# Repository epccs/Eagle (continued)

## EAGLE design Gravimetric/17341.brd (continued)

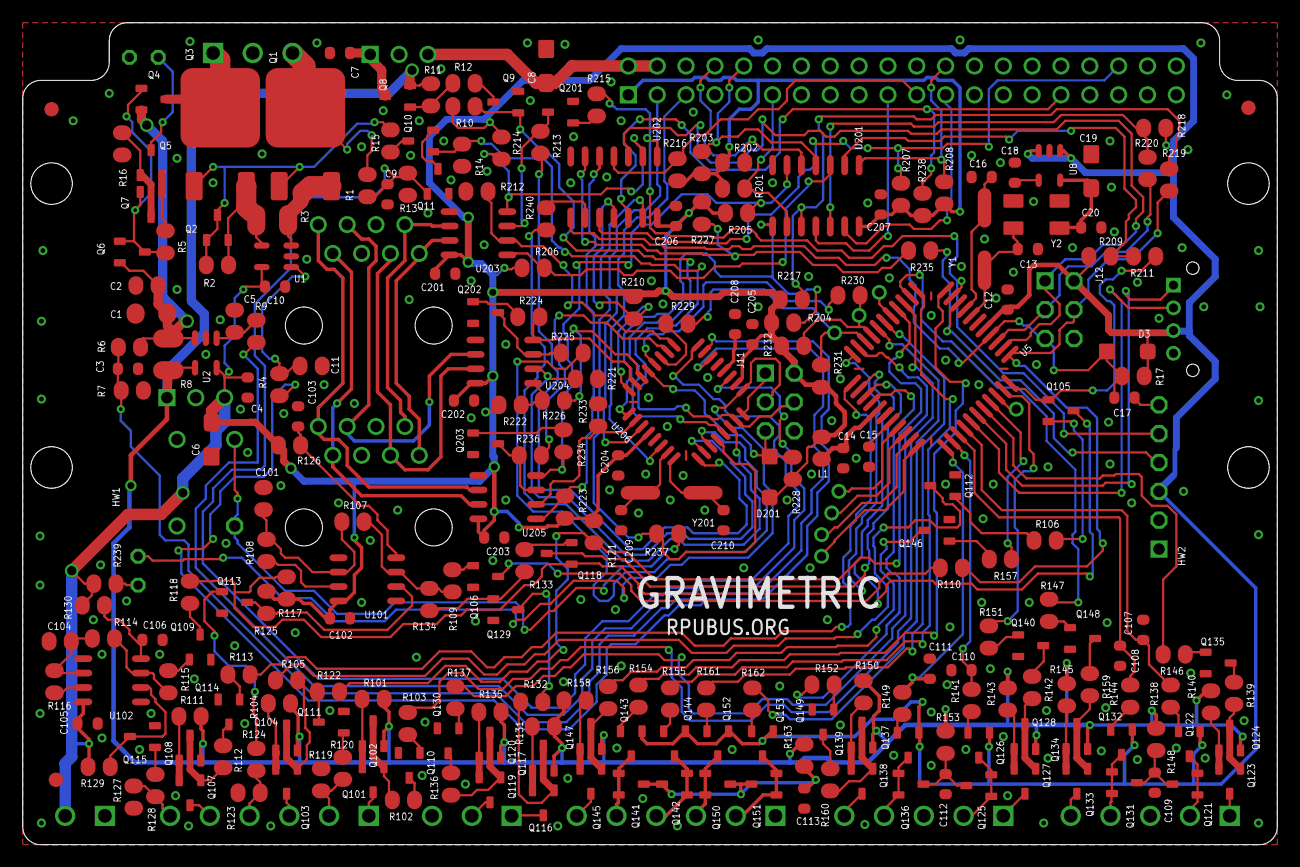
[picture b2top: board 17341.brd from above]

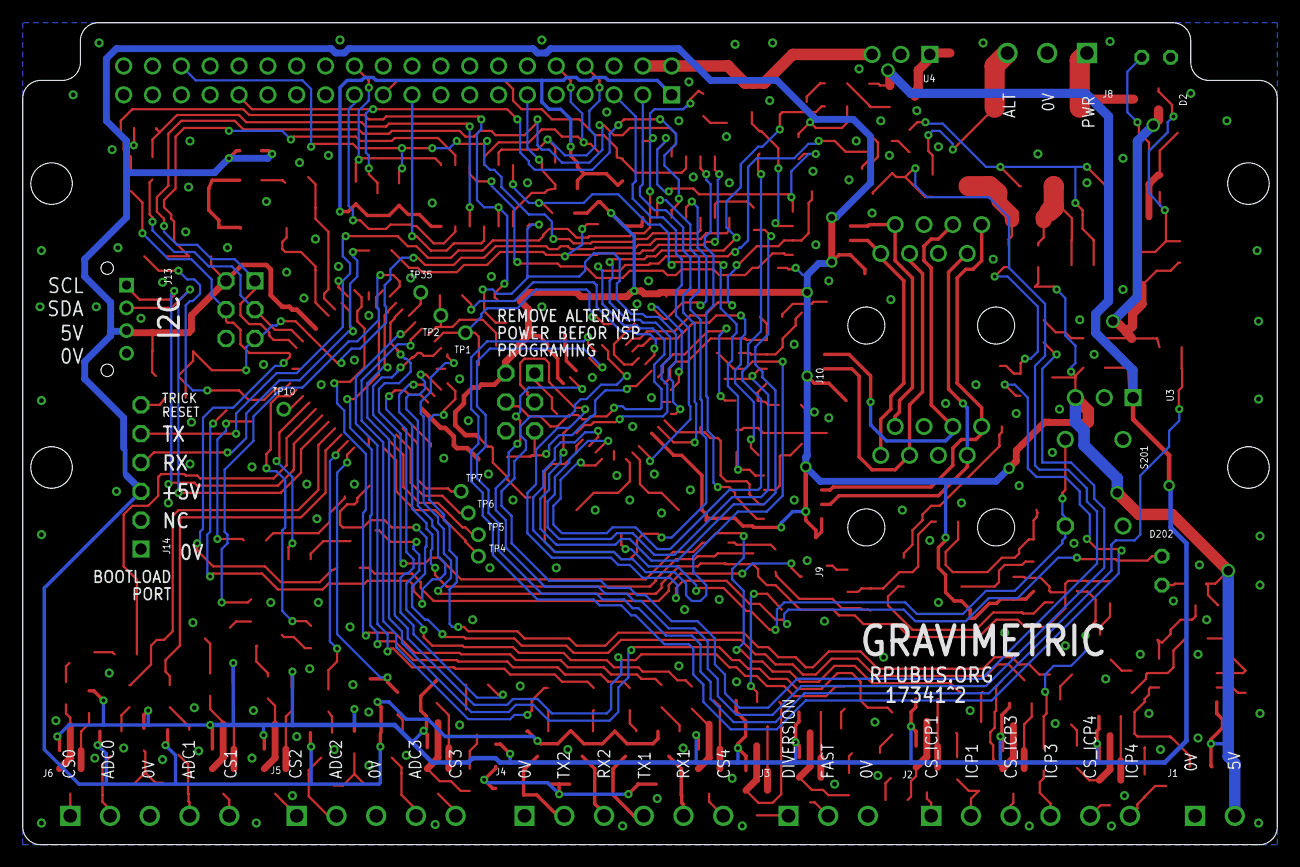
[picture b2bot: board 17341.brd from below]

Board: 2 copper layers, 110.5 x 72.4 mm, 281 parts (26 on the bottom side), 219 nets.

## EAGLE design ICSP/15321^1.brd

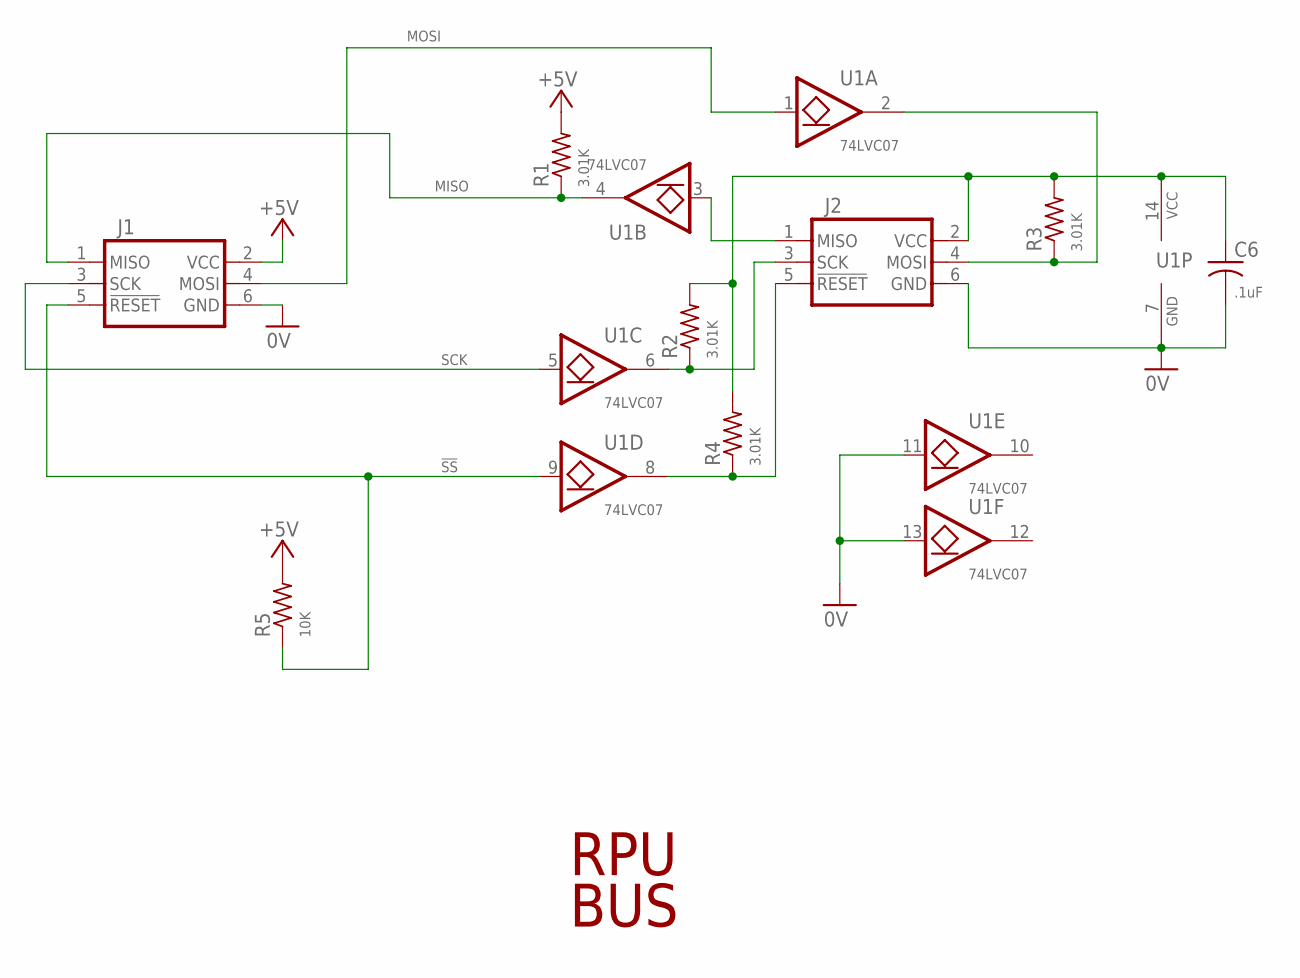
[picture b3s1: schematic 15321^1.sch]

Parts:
C6: .1uF; C0603(1608)
J1, J2: ISP-SPIEDG; ISP-EDG
R1, R2, R3, R4: 3.01K; C0805(2012)
R5: 10K; C0805(2012)
U1: 74LVC07; 14SOIC

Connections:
0V: C6.2, J1.6 (GND), J2.6 (GND), U1.7 (GND), U1.11 (I), U1.13 (I)
!SS: J1.5 (!RESET), R5.1, U1.9 (I)
+5V: J1.2 (VCC), R1.2, R5.2
MISO: J1.1 (MISO), R1.1, U1.4 (O)
MOSI: J1.4 (MOSI), U1.1 (I)
unnamed: J2.3 (SCK), R2.1, U1.6 (O)
unnamed: J2.1 (MISO), U1.3 (I)
unnamed: J2.4 (MOSI), R3.1, U1.2 (O)
unnamed: J2.5 (!RESET), R4.1, U1.8 (O)
SCK: J1.3 (SCK), U1.5 (I)
VCC: C6.1, J2.2 (VCC), R2.2, R3.2, R4.2, U1.14 (VCC)

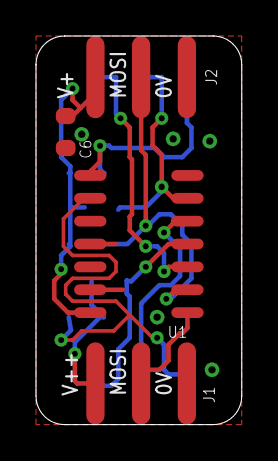
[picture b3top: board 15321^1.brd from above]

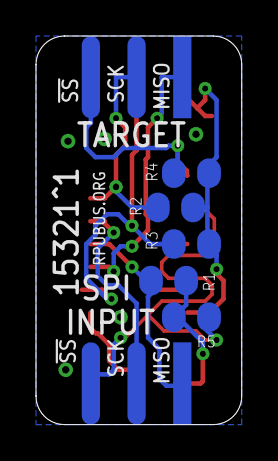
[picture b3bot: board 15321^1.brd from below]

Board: 2 copper layers, 11.4 x 21.6 mm, 9 parts (5 on the bottom side), 11 nets.

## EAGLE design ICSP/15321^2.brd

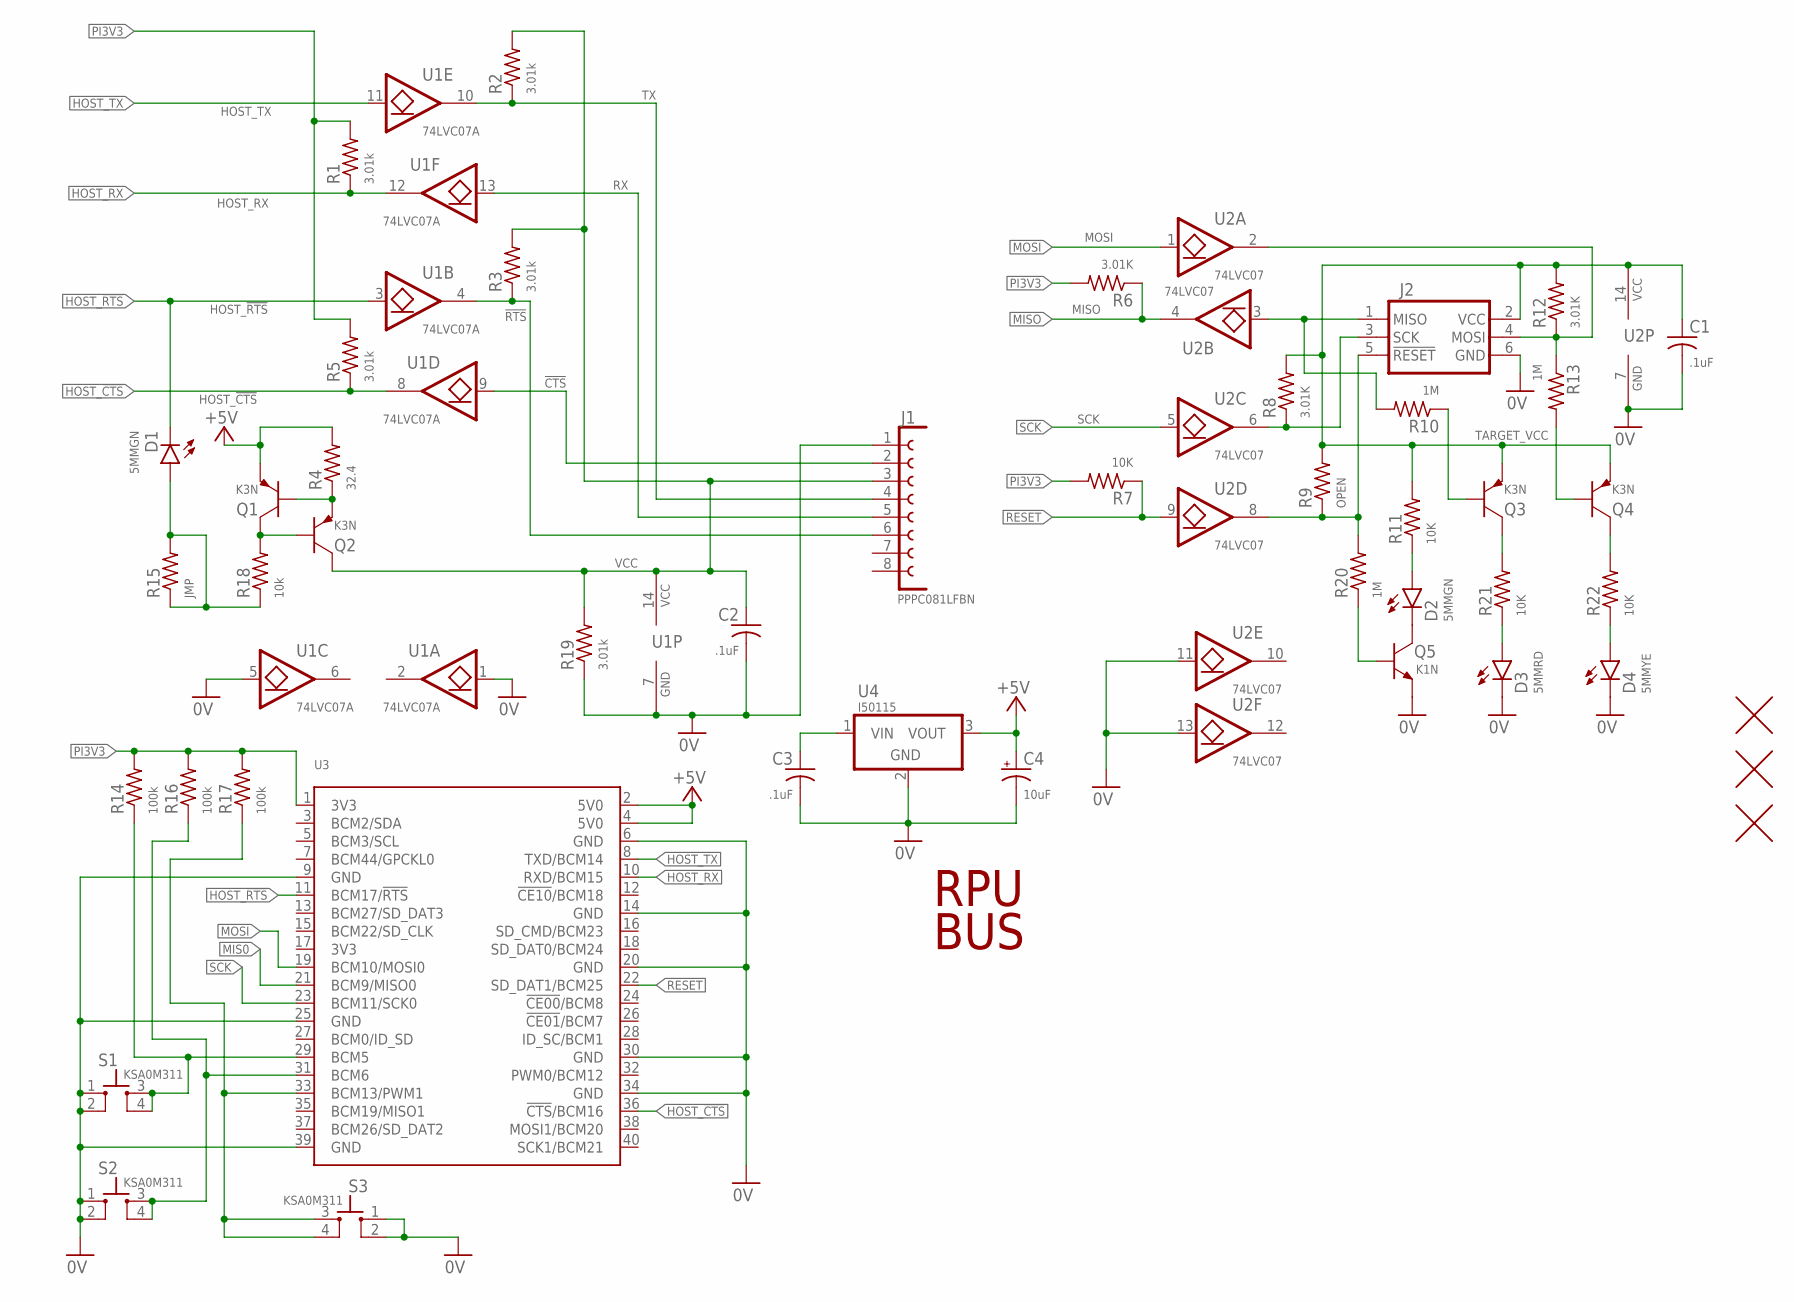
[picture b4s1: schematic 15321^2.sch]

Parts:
C1, C2, C3: .1uF; C0603(1608)
C4: 10uF; 3216
D1, D2: 5MMGN; LED5MM
D3: 5MMRD; LED5MM
D4: 5MMYE; LED5MM
J1: PPPC081LFBN; F1X8
J2: ISP-SPIEDG; ISP-EDG
Q1, Q2, Q3, Q4: K3N; SOT23
Q5: K1N; SOT23
R1, R2, R3, R5, R19: 3.01k; C0805(2012)
R4: 32.4; C0805(2012)
R6, R8, R12: 3.01K; C0805(2012)
R7, R11, R21, R22: 10K; C0805(2012)
R9: OPEN; C0805(2012)
R10, R13, R20: 1M; C0805(2012)
R14, R16, R17: 100k; C0805(2012)
R15: JMP; C0805(2012)
R18: 10k; C0805(2012)
S1, S2, S3: KSA0M311; 0M311
U1: 74LVC07A; 14SOIC
U2: 74LVC07; 14SOIC
U3: RPI-ZERO; RASPI_ZERO_H40PIN
U4: I50115; OKI-78SR-H
U$2, U$3, U$4: FIDUCIAL1.27; FIDUCIAL-1.27

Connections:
0V: C1.2, C2.2, C3.2, C4.-, D3.K, D4.K, J1.1, J2.6 (GND), Q5.E, R19.1, S1.1, S1.2, S2.1, S2.2, S3.1, S3.2, U1.1 (I), U1.5 (I), U1.7 (GND), U2.7 (GND), U2.11 (I), U2.13 (I), U3.6 (GND), U3.9 (GND), U3.14 (GND), U3.20 (GND), U3.25 (GND), U3.30 (GND), U3.34 (GND), U3.39 (GND), U4.2 (GND)
!CTS: J1.2, U1.9 (I)
!RST: J2.5 (!RESET), R9.1, R20.2, U2.8 (O)
!RTS: J1.6, R3.1, U1.4 (O)
+5V: C4.+, Q1.E, R4.2, U3.2 (5V0), U3.4 (5V0), U4.3 (VOUT)
HOST_!CTS: R5.1, U1.8 (O), U3.36 (!CTS!/BCM16)
HOST_!RTS: D1.K, U1.3 (I), U3.11 (BCM17/!RTS!)
HOST_RX: R1.1, U1.12 (O), U3.10 (RXD/BCM15)
HOST_TX: U1.11 (I), U3.8 (TXD/BCM14)
MIS0: U3.21 (BCM9/MISO0)
MISO: R6.1, U2.4 (O)
MOSI: U2.1 (I), U3.19 (BCM10/MOSI0)
unnamed: J2.3 (SCK), R8.1, U2.6 (O)
unnamed: D4.A, R22.1
unnamed: J2.1 (MISO), R10.2, U2.3 (I)
unnamed: J2.4 (MOSI), R12.1, R13.1, U2.2 (O)
unnamed: Q4.C, R22.2
unnamed: D3.A, R21.1
unnamed: Q3.C, R21.2
unnamed: Q1.B, Q2.E, R4.1
unnamed: Q1.C, Q2.B, R18.2
unnamed: D1.A, R15.1, R15.2, R18.1
unnamed: Q5.B, R20.1
unnamed: D2.K, Q5.C
unnamed: R14.1, S1.3, S1.4, U3.29 (BCM5)
unnamed: R16.1, S2.3, S2.4, U3.31 (BCM6)
unnamed: R17.1, S3.3, S3.4, U3.33 (BCM13/PWM1)
unnamed: D2.A, R11.1
unnamed: Q4.B, R13.2
unnamed: Q3.B, R10.1
PI3V3: R1.2, R5.2, R6.2, R7.2, R14.2, R16.2, R17.2, U3.1 (3V3)
RESET: R7.1, U2.9 (I), U3.22 (SD_DAT1/BCM25)
RX: J1.5, U1.13 (I)
SCK: U2.5 (I), U3.23 (BCM11/SCK0)
TARGET_VCC: C1.1, J2.2 (VCC), Q3.E, Q4.E, R8.2, R9.2, R11.2, R12.2, U2.14 (VCC)
TX: J1.4, R2.1, U1.10 (O)
VCC: C2.1, J1.3, Q2.C, R2.2, R3.2, R19.2, U1.14 (VCC)
VIN: C3.1, U4.1 (VIN)

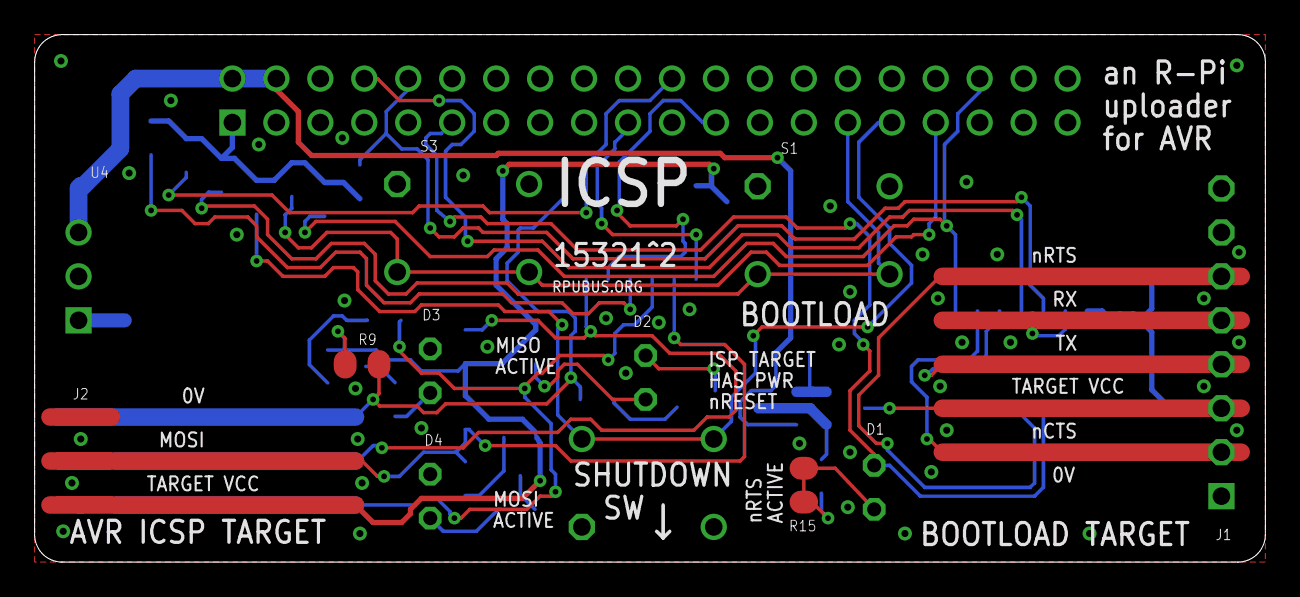
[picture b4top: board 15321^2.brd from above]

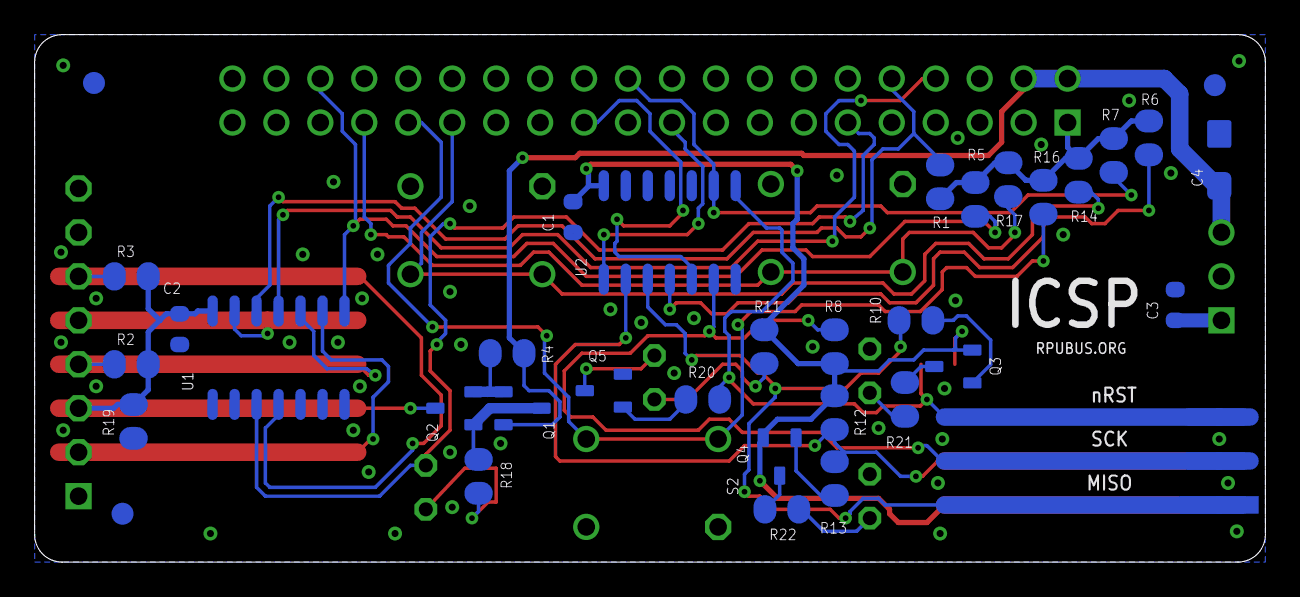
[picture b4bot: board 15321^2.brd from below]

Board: 2 copper layers, 71.1 x 30.5 mm, 47 parts (35 on the bottom side), 37 nets.

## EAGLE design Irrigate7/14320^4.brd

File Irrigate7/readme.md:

[Irrigate7]

This circuit board is for Irrigation control.

[Irrigate7]: https://github.com/epccs/Irrigate7

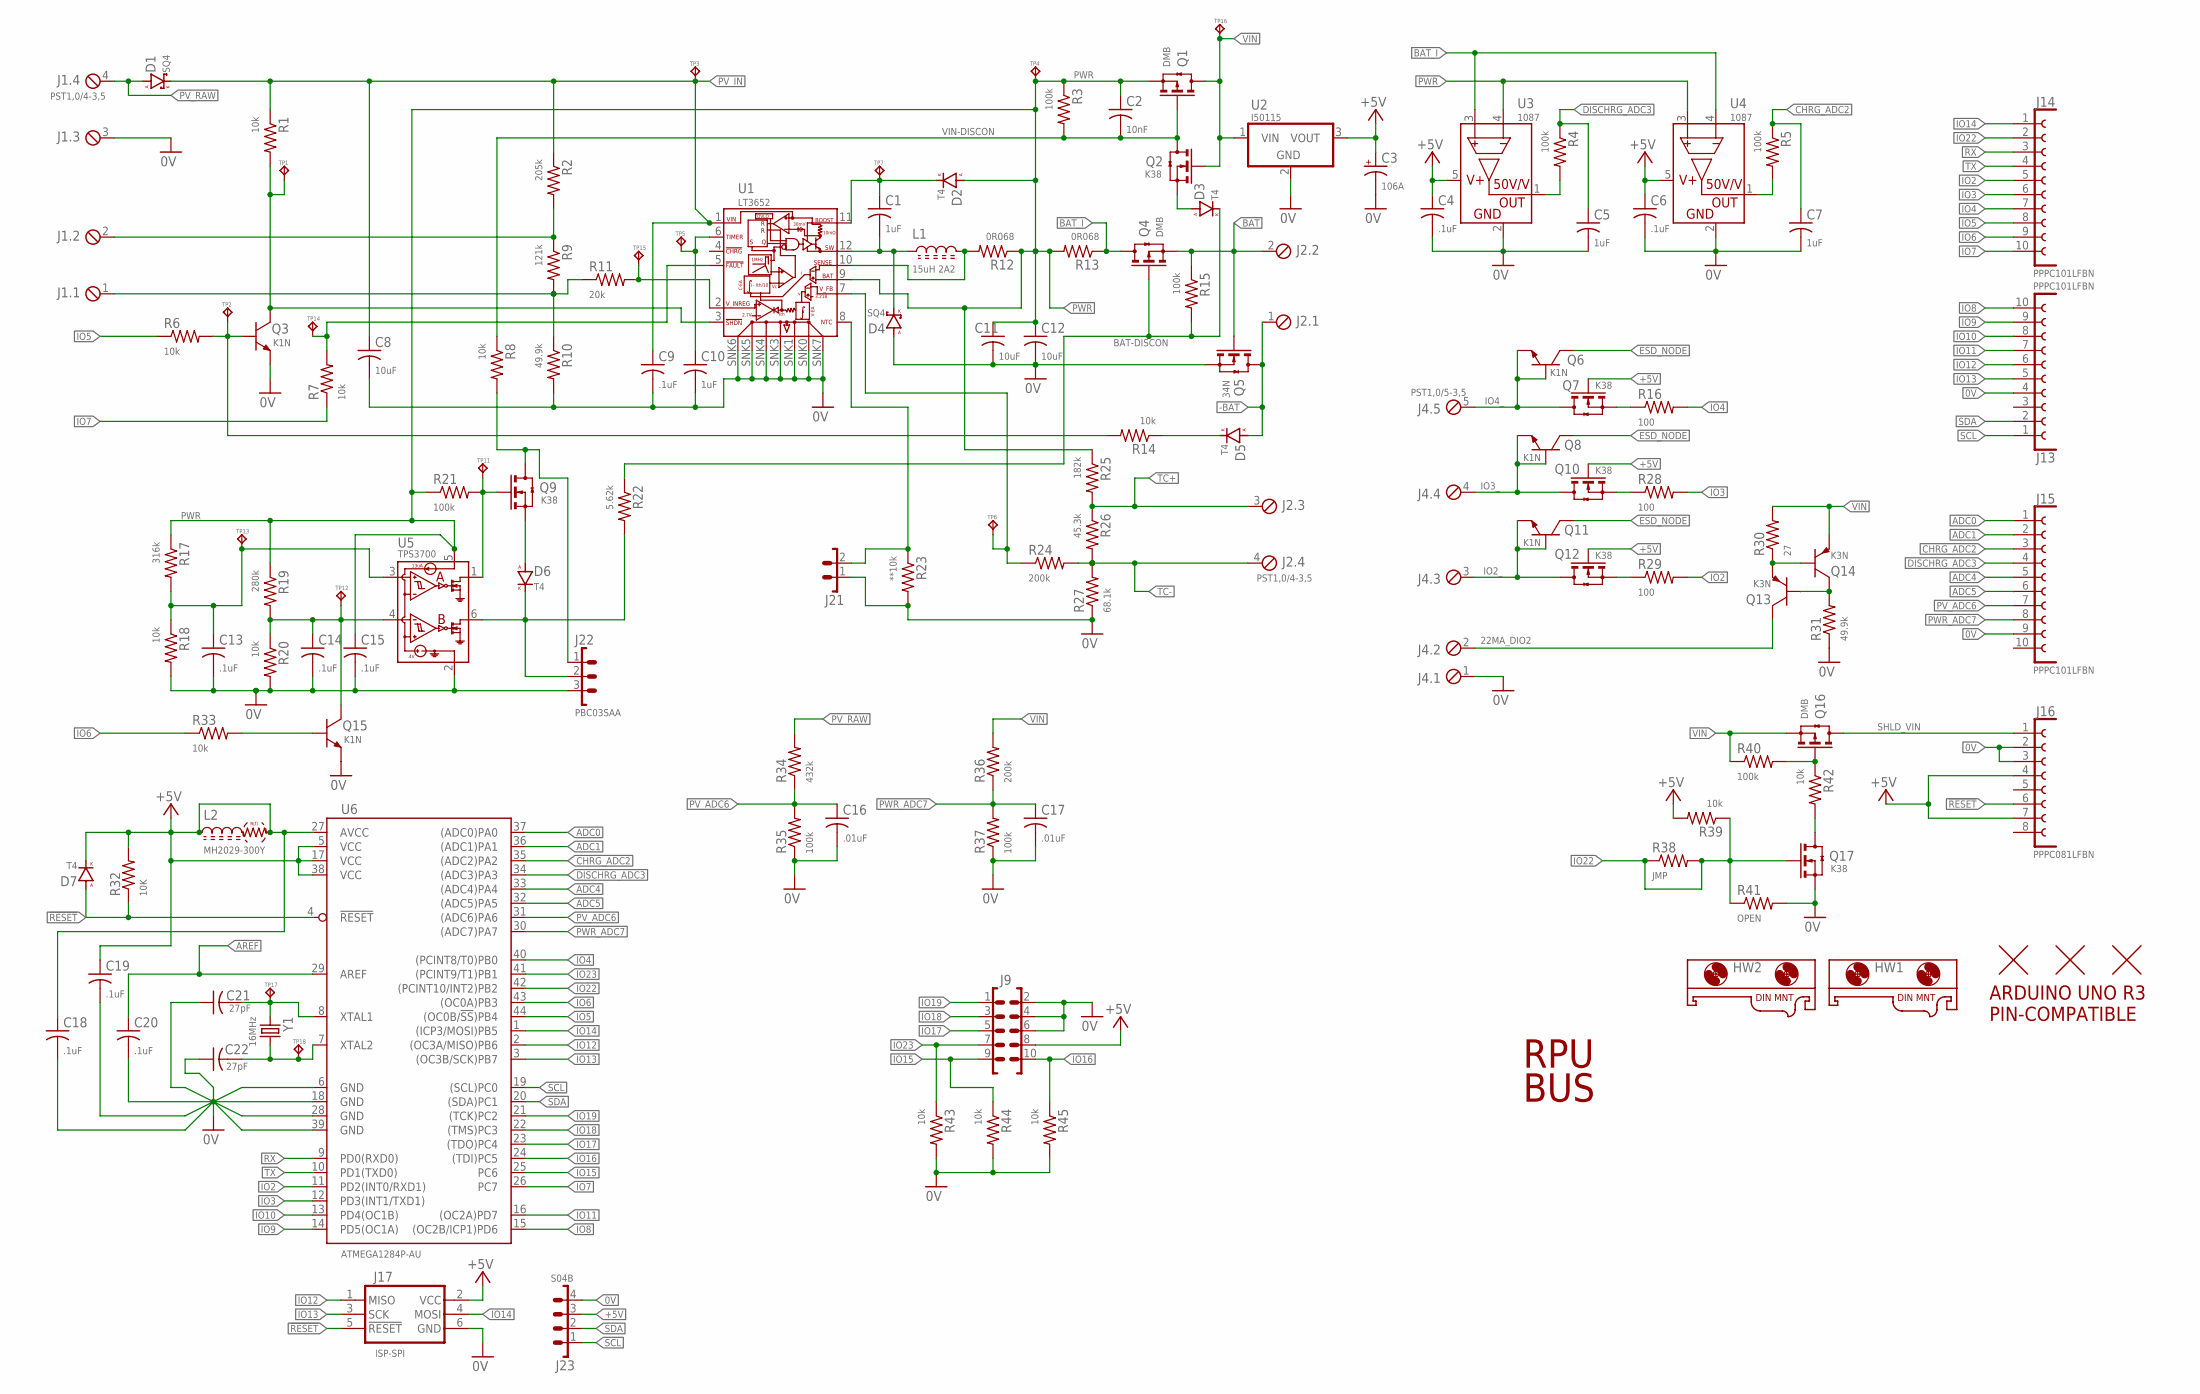
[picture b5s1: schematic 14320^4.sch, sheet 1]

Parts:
C1, C5, C7, C10: 1uF; C0805(2012)
C2: 10nF; C0603(1608)
C3: 106A; 3216
C4, C6, C13, C14, C15, C18, C19, C20: .1uF; C0603(1608)
C8, C11, C12: 10uF; C1206(3216)
C9: .1uF; C0805(2012)
C16, C17: .01uF; C0603(1608)
C21, C22: 27pF; C0603(1608)
D1, D4: SQ4; SMA
D2, D3, D5, D6, D7: T4; SOD123
HW1, HW2: MOUNT-HOLE5.0; USA10
HW3: ARDUINO-UNO; ARDUINO_UNO
J1, J2: PST1,0/4-3,5; MCV4
J4: PST1,0/5-3,5; MCV5
J9: 2X5
J13, J14, J15: PPPC101LFBN; F1X10
J16: PPPC081LFBN; F1X8
J17: ISP-SPI; ISP
J21: 1X2
J22: PBC03SAA; 1X3
J23: S04B; B04B
L1: 15uH 2A2; L3939
L2: MH2029-300Y; C0805(2012)
Q1, Q4, Q16: DMB; SOT23
Q2, Q7, Q9, Q10, Q12, Q17: K38; SOT23
Q3, Q6, Q8, Q11, Q15: K1N; SOT23
Q5: 34N; SOT23
Q13, Q14: K3N; SOT23
R1, R6, R7, R8, R14, R18, R20, R33, R39, R42, R43, R44, R45: 10k; C0805(2012)
R2: 205k; C0805(2012)
R3, R4, R5, R15, R21, R35, R37, R40: 100k; C0805(2012)
R9: 121k; C0805(2012)
R10, R31: 49.9k; C0805(2012)
R11: 20k; C0805(2012)
R12, R13: 0R068; C1210(3225)
R16, R28, R29: 100; C0805(2012)
R17: 316k; C0805(2012)
R19: 280k; C0805(2012)
R22: 5.62k; C0805(2012)
R23: **10k; C0805(2012)
R24, R36: 200k; C0805(2012)
R25: 182k; C0805(2012)
R26: 45.3k; C0805(2012)
R27: 68.1k; C0805(2012)
R30: 27; C0805(2012)
R32: 10K; C0805(2012)
R34: 432k; C0805(2012)
R38: JMP; C0805(2012)
R41: OPEN; C0805(2012)
TP1, TP2, TP3, TP4, TP5, TP6, TP7, TP11, TP12, TP13, TP14, TP15, TP16, TP17, TP18: TPPAD1-08; P1-08
U1: LT3652; 12MSOP-EDP-HAND
U2: I50115; OKI-78SR-H
U3, U4: 1087; SOT23-5
U5: TPS3700; SOT23-6
U6: ATMEGA1284P-AU; TQFP44
U$2, U$3, U$4: FIDUCIAL1.27; FIDUCIAL-1.27
Y1: 16MHz; CSM-3X

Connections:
0V: C3.-, C4.2, C5.2, C6.2, C7.2, C8.2, C9.2, C10.2, C11.2, C12.2, C13.2, C14.2, C15.2, C16.2, C17.2, C18.2, C19.2, C20.2, C21.1, C22.1, D4.A, J1.3, J4.1, J9.2, J9.4, J9.6, J13.4, J15.9, J16.2, J16.3, J17.6 (GND), J21.1, J22.3, J23.4, Q3.E, Q5.2(S) (S), Q15.E, Q17.2(S) (S), R10.2, R18.2, R20.2, R23.2, R27.1, R31.1, R35.1, R37.1, R41.2, R43.2, R44.2, R45.2, U1.SNK0 (0V), U1.SNK1 (0V), U1.SNK3 (0V), U1.SNK4 (0V), U1.SNK5 (0V), U1.SNK6 (0V), U1.SNK7 (0V), U2.2 (GND), U3.2 (GND), U4.2 (GND), U5.2 (0V), U6.6 (GND), U6.18 (GND), U6.28 (GND), U6.39 (GND); also elsewhere on the board
22MA_DIO2: J4.2, Q13.C
!RESET!: D7.A, J16.6, J17.5 (!RESET), R32.1, U6.4 (!RESET)
+5V: C3.+, C4.1, C6.1, C18.1, C19.1, D7.C (K), J9.8, J16.4, J16.7, J17.2 (VCC), J23.3, L2.1, L2.2, Q7.1(G) (G), Q10.1(G) (G), Q12.1(G) (G), R32.2, R39.2, U2.3 (VOUT), U3.5 (VCC), U4.5 (VCC), U6.5 (VCC), U6.17 (VCC), U6.27 (AVCC), U6.38 (VCC); also elsewhere on the board
-BAT: D5.A, J2.1, Q5.3(D) (D)
ADC0: J15.1, U6.37 ((ADC0)PA0); also elsewhere on the board
ADC1: J15.2, U6.36 ((ADC1)PA1); also elsewhere on the board
ADC4: J15.5, U6.33 ((ADC4)PA4); also elsewhere on the board
ADC5: J15.6, U6.32 ((ADC5)PA5); also elsewhere on the board
AREF: C20.1, U6.29 (AREF)
BAT: J2.2, Q4.2(S) (S), Q5.1(G) (G), R15.1
BAT-DISCON: D3.C (K), Q4.1(G) (G), R15.2, R22.1
BAT_I: Q4.3(D) (D), R13.1, U3.3 (S+), U4.4 (S-)
CHRG_ADC2: C7.1, J15.3, R5.1, U6.35 ((ADC2)PA2)
DISCHRG_ADC3: C5.1, J15.4, R4.1, U6.34 ((ADC3)PA3)
ESD_NODE: Q6.C, Q8.C, Q11.C; also elsewhere on the board
IO2: J14.5, R29.2, U6.11 (PD2(INT0/RXD1))
IO2_: J4.3, Q11.B, Q11.E, Q12.3(D) (D)
IO3: J14.6, R28.2, U6.12 (PD3(INT1/TXD1))
IO3_: J4.4, Q8.B, Q8.E, Q10.3(D) (D)
IO4: J14.7, R16.2, U6.40 ((PCINT8/T0)PB0)
IO4_: J4.5, Q6.B, Q6.E, Q7.3(D) (D)
IO5: J14.8, R6.1, U6.44 ((OC0B/!SS!)PB4)
IO6: J14.9, R33.1, U6.43 ((OC0A)PB3)
IO7: J14.10, R7.1, U6.26 (PC7)
IO8: J13.10, U6.15 ((OC2B/ICP1)PD6); also elsewhere on the board
IO9: J13.9, U6.14 (PD5(OC1A)); also elsewhere on the board
IO10: J13.8, U6.13 (PD4(OC1B)); also elsewhere on the board
IO11: J13.7, U6.16 ((OC2A)PD7); also elsewhere on the board
IO12: J13.6, J17.1 (MISO), U6.2 ((OC3A/MISO)PB6); also elsewhere on the board
IO13: J13.5, J17.3 (SCK), U6.3 ((OC3B/SCK)PB7); also elsewhere on the board
IO14: J14.1, J17.4 (MOSI), U6.1 ((ICP3/MOSI)PB5); also elsewhere on the board
IO15: J9.9, R44.1, U6.25 (PC6); also elsewhere on the board
IO16: J9.10, R45.1, U6.24 ((TDI)PC5); also elsewhere on the board
IO17: J9.5, U6.23 ((TDO)PC4); also elsewhere on the board
IO18: J9.3, U6.22 ((TMS)PC3); also elsewhere on the board
IO19: J9.1, U6.21 ((TCK)PC2); also elsewhere on the board
IO22: J14.2, Q17.1(G) (G), R38.1, R38.2, R39.1, R41.1, U6.42 ((PCINT10/INT2)PB2)
IO23: J9.7, R43.1, U6.41 ((PCINT9/T1)PB1); also elsewhere on the board
unnamed: R24.1, TP6.TP, U1.7 (V_FB)
unnamed: Q16.1(G) (G), R40.2, R42.1
unnamed: Q17.3(D) (D), R42.2
unnamed: R4.2, U3.1 (OUT)
unnamed: C1.1, D2.C (K), TP7.TP, U1.11 (BOOST)
unnamed: C10.1, TP5.TP, U1.6 (TIMER)
unnamed: R5.2, U4.1 (OUT)
unnamed: D5.C (K), R14.1
unnamed: J1.1, R9.2, R10.1, R11.1
unnamed: Q3.C, R1.2, TP1.TP, U1.3 (!SHDN)
unnamed: Q3.B, R6.2, R14.2, TP2.TP
unnamed: Q15.B, R33.2
unnamed: C14.1, Q15.C, R19.2, R20.1, TP12.TP, U5.4 (INB)
unnamed: D3.A, Q2.2(S) (S)
unnamed: J1.2, R2.2, R9.1
unnamed: D6.A, Q9.2(S) (S)
unnamed: C13.1, R17.2, R18.1, TP13.TP, U5.3 (INA)
unnamed: Q9.1(G) (G), R21.2, TP11.TP, U5.1 (OUTA)
unnamed: D6.C (K), J22.2, R22.2, U5.6 (OUTB)
unnamed: J22.1, Q9.3(D) (D), R8.2
unnamed: R11.2, TP15.TP, U1.2 (V_INREG)
unnamed: Q13.E, Q14.B, R30.1
unnamed: Q10.2(S) (S), R28.1
unnamed: Q13.B, Q14.C, R31.2
unnamed: Q7.2(S) (S), R16.1
unnamed: R7.2, TP14.TP, U1.5 (!FAULT)
unnamed: Q12.2(S) (S), R29.1
unnamed: C21.2, TP17.TP, U6.8 (XTAL1), Y1.1
unnamed: C22.2, TP18.TP, U6.7 (XTAL2), Y1.2
NTC1: J21.2, R23.1, U1.8 (NTC)
PV_ADC6: C16.1, J15.7, R34.1, R35.2, U6.31 ((ADC6)PA6)
PV_IN: C8.1, C9.1, D1.K, R1.1, R2.1, TP3.TP, U1.1 (VIN)
PV_RAW: D1.A, J1.4, R34.2
PWR: C2.1, C11.1, C12.1, C15.1, D2.A, Q1.2(S) (S), R3.1, R12.1, R13.2, R17.1, R19.1, R21.1, R25.1, TP4.TP, U1.9 (BAT), U3.4 (S-), U4.3 (S+), U5.5 (VDD)
PWR_ADC7: C17.1, J15.8, R36.1, R37.2, U6.30 ((ADC7)PA7)
RX: J14.3, U6.9 (PD0(RXD0))
SCL: J13.1, J23.1, U6.19 ((SCL)PC0)
SDA: J13.2, J23.2, U6.20 ((SDA)PC1)
SENSE1: L1.2, R12.2, U1.10 (SENSE)
SHLD_VIN: J16.1, Q16.3(D) (D)
SW: C1.2, D4.K, L1.1, U1.12 (SW)
TC+: J2.3, R25.2, R26.1
TC-: J2.4, R24.2, R26.2, R27.2
TX: J14.4, U6.10 (PD1(TXD0))
VIN: Q1.3(D) (D), Q2.1(G) (G), Q14.E, Q16.2(S) (S), R30.2, R36.2, R40.1, TP16.TP, U2.1 (VIN); also elsewhere on the board
VIN-DISCON: C2.2, Q1.1(G) (G), Q2.3(D) (D), R3.2, R8.1
